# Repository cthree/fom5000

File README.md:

# Feed-O-Matic 5000
An IoT hack of the PetMate automatic pet feeder to add logging, control and hopper status over the Internet.

This project is very much an early work in progress.

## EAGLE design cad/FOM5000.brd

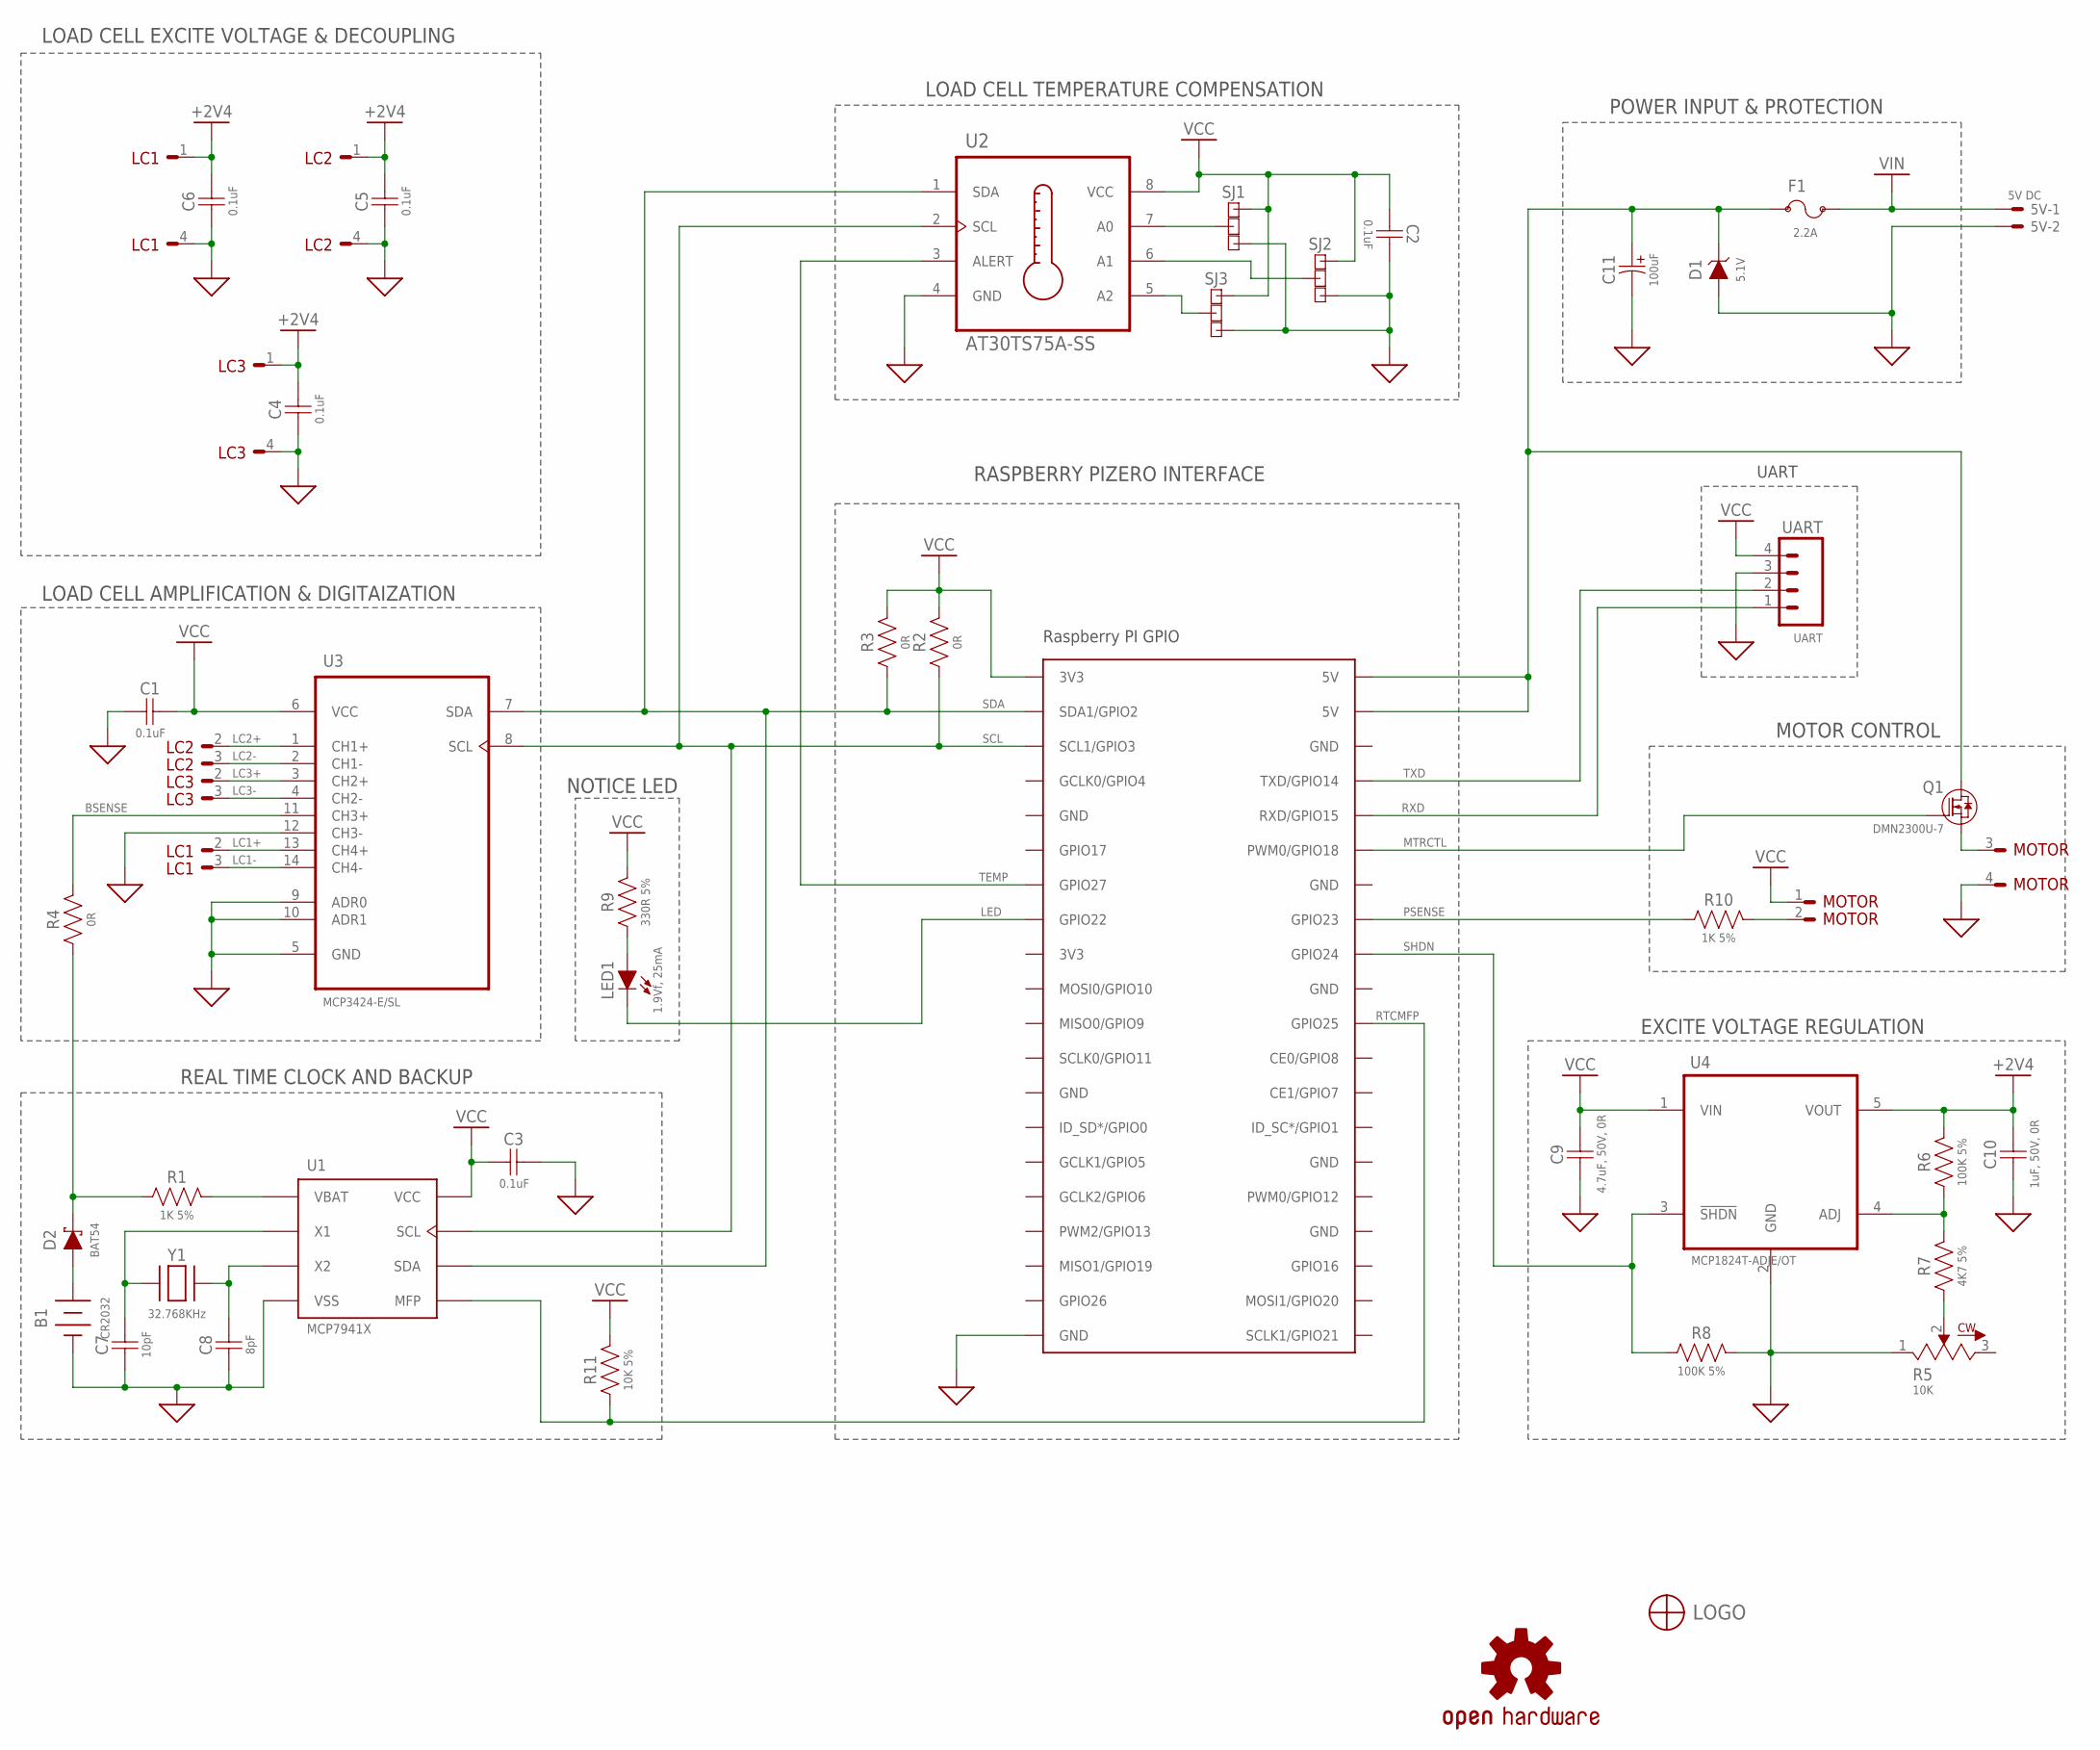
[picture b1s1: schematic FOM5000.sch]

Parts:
5V: 5V DC; PTS1_5/2-5_0-H-NOIND
B1: CR2032; BU2032SM-HD
C1, C2, C3, C4, C5, C6: 0.1uF; 18-0603
C7: 10pF; 18-0603
C8: 8pF; 18-0603
C9: 4.7uF, 50V, 0R; 31-1206
C10: 1uF, 50V, 0R; 21-0805
C11: 100uF; 8MM_SMD
D1: 5.1V; DO-214AA
D2: BAT54; SOT23-3
F1: 2.2A; 1206
LC1, LC2, LC3: B4B-PH-K-S
LED1: 1.9Vf, 25mA; LED5MM
LOGO: REDDOG-LOGOSILK; REDDOG-LOGO-SILK
LOGO1: OSHW-LOGOL; OSHW-LOGO-L
MOTOR: B4B-PH-K-S
PI: RPI2; 100-2X20-TH-040
Q1: DMN2300U-7; SOT23-3
R1, R10: 1K 5%; R0603
R2, R3, R4: 0R; R0603
R5: 10K; 3296W
R6, R8: 100K 5%; R0603
R7: 4K7 5%; R0603
R9: 330R 5%; R0603
R11: 10K 5%; R0603
SJ1, SJ2, SJ3: SOLDERJUMPER_2WAYPASTE2&3; SJ_3_PASTE2&3
U1: MCP7941X; SOIC8-N_MC
U2: AT30TS75A-SS; SOIC8-N_MC
U3: MCP3424-E/SL; SOIC127P600X175-14N
U4: MCP1824T-ADJE/OT; SOT95P270X145-5N
UART: UART; 100-1X04-TH-040
Y1: 32.768KHz; 4-SOJ

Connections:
5V: C11.P (POS), D1.C, F1.1, PI.2 (5V), PI.4 (5V), Q1.3 (D)
+2V4: C4.2, C5.2, C6.2, C10.2, LC1.1, LC2.1, LC3.1, R6.2, U4.5 (VOUT)
ADJ: R6.1, R7.2, U4.4 (ADJ)
BSENSE: R4.2, U3.11 (CH3+)
GND: 5V.2, B1.N (GND), C1.1, C2.2, C3.2, C4.1, C5.1, C6.1, C7.1, C8.1, C9.1, C10.1, C11.N (NEG), D1.A, LC1.4, LC2.4, LC3.4, MOTOR.4, PI.6 (GND), PI.9 (GND), PI.14 (GND), PI.20 (GND), PI.25 (GND), PI.30 (GND), PI.34 (GND), PI.39 (GND), R5.1, R8.2, SJ1.3, SJ2.3, SJ3.3, U1.4 (VSS), U2.4 (GND), U3.5 (GND), U3.9 (ADR0), U3.10 (ADR1), U3.12 (CH3-), U4.2 (GND), UART.3
LC1+: LC1.2, U3.13 (CH4+)
LC1-: LC1.3, U3.14 (CH4-)
LC2+: LC2.2, U3.1 (CH1+)
LC2-: LC2.3, U3.2 (CH1-)
LC3+: LC3.2, U3.3 (CH2+)
LC3-: LC3.3, U3.4 (CH2-)
LED: LED1.K (C), PI.15 (GPIO22)
MTRCTL: PI.12 (PWM0/GPIO18), Q1.1 (G)
unnamed: D2.C, R1.1, R4.1
unnamed: R5.2, R7.1
unnamed: LED1.A, R9.1
unnamed: MOTOR.2, R10.2
unnamed: MOTOR.3, Q1.2 (S)
PSENSE: PI.16 (GPIO23), R10.1
RTCMFP: PI.22 (GPIO25), R11.1, U1.7 (MFP)
RXD: PI.10 (RXD/GPIO15), UART.1
SCL: PI.5 (SCL1/GPIO3), R2.1, U1.6 (SCL), U2.2 (SCL), U3.8 (SCL)
SDA: PI.3 (SDA1/GPIO2), R3.1, U1.5 (SDA), U2.1 (SDA), U3.7 (SDA)
SHDN: PI.18 (GPIO24), R8.1, U4.3 (!SHDN)
TA0: SJ1.2, U2.7 (A0)
TA1: SJ2.2, U2.6 (A1)
TA2: SJ3.2, U2.5 (A2)
TEMP: PI.13 (GPIO27), U2.3 (ALERT)
TXD: PI.8 (TXD/GPIO14), UART.2
VBAT: B1.P (VBAT), D2.A
VBAT_IN: R1.2, U1.3 (VBAT)
VCC: C1.2, C2.1, C3.1, C9.2, MOTOR.1, PI.1 (3V3), R2.2, R3.2, R9.2, R11.2, SJ1.1, SJ2.1, SJ3.1, U1.8 (VCC), U2.8 (VCC), U3.6 (VCC), U4.1 (VIN), UART.4
VIN: 5V.1, F1.2
Y1: C7.2, U1.1 (X1), Y1.1 (A)
Y2: C8.2, U1.2 (X2), Y1.4 (B)

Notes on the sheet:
UART
MOTOR CONTROL
POWER INPUT & PROTECTION
LOAD CELL EXCITE VOLTAGE & DECOUPLING
LOAD CELL AMPLIFICATION & DIGITAIZATION
LOAD CELL TEMPERATURE COMPENSATION
REAL TIME CLOCK AND BACKUP
NOTICE LED
EXCITE VOLTAGE REGULATION
RASPBERRY PIZERO INTERFACE

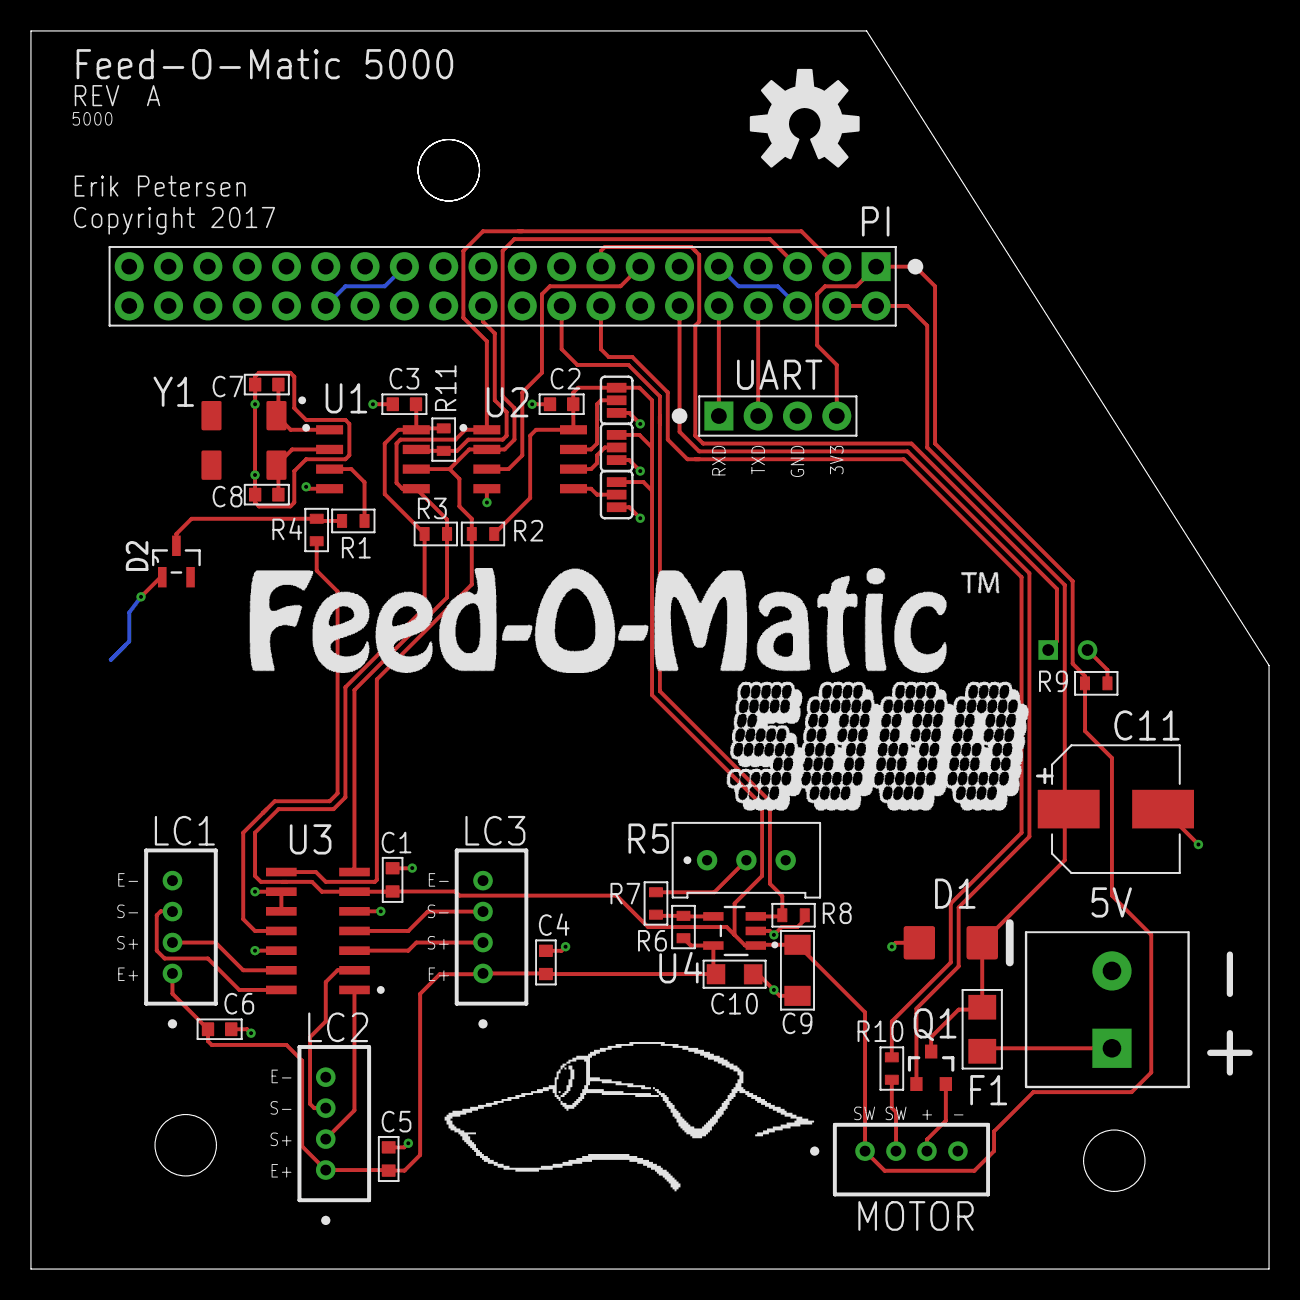
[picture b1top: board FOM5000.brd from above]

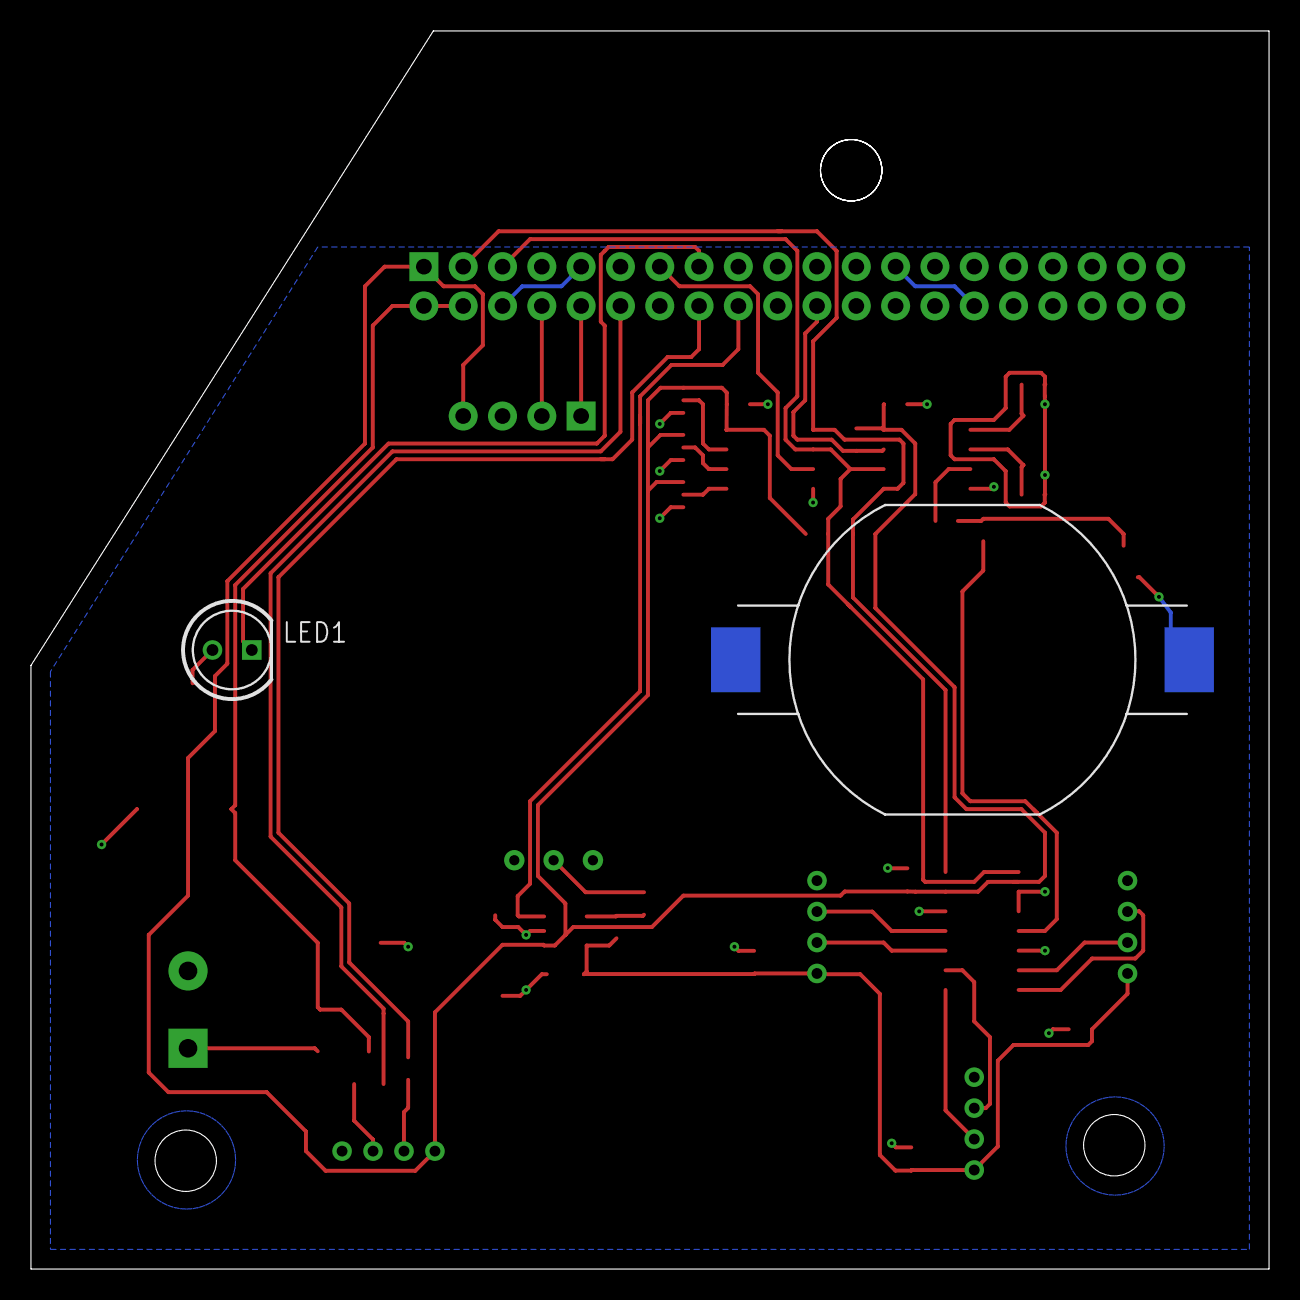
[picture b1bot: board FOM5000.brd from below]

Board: 2 copper layers, 80.0 x 80.0 mm, 45 parts (2 on the bottom side), 35 nets.

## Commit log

2017-04-11 initial commit of cad files
2017-04-11 Rev A Complete
2017-04-11 Add pullup resistor on RTCMFP
2017-04-11 Rename mislabeled net RTCMFP
2017-04-11 Add schematic and PCB PDFs
2017-04-11 Add some initial project docs using hugo
2017-04-11 Fix URL oops in docs config
2017-04-11 Add some initial project docs using hugo
    Fix URL oops in docs config
    regen the docs
2017-04-11 Fix base url
2017-04-11 Add schottky diode on VBAT for UL compliance; change VBAT load limiting resistor to 1K per AN-1365
2017-04-12 Added some input capacitance
2017-04-18 Change R9 to 330R

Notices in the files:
cad/FOM5000.brd:
Designed by Erik Petersen - Copyright 2017
COPYRIGHT: Copyright 2017
